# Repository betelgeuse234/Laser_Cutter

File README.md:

# Laser_Cutter
Roughly 2'x4' laser cutter with custom software and electronics hardware

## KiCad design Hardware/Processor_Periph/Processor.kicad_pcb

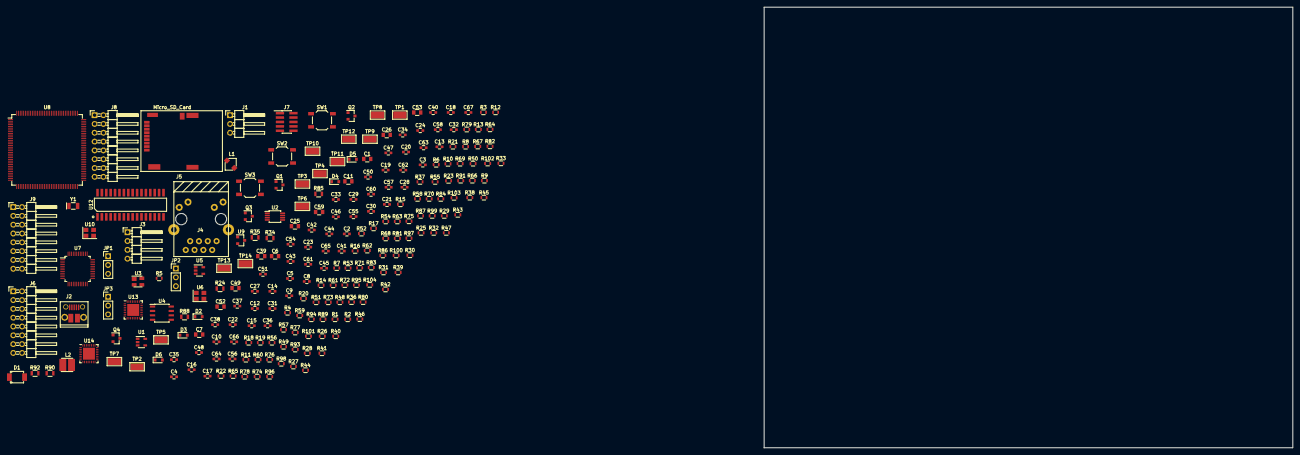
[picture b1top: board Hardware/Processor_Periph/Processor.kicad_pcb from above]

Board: 4 copper layers, 152.4 x 127.0 mm, 226 parts (0 on the bottom side), 183 nets, no tracks yet.

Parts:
C1, C25, C49, C59: 4.7uF; C_0805
C2, C4, C5, C10, C12, C14, C15, C16, C18, C19, C20, C22, C23, C24, C27, C29, C30, C31, C33, C34, C35, C37, C38, C40, C42, C43, C44, C46, C47, C48, C50, C51, C54, C55, C57, C58, C60, C61, C62, C63, C64, C65, C66, C67: 100nF; C_0603
C3: 4.5nF; C_0603
C6, C11: 1uF; C_0805
C7, C26, C39, C53: 10uF; C_0805
C8, C9: 3.9pF; C_0603
C13, C17, C21, C28, C32, C36, C41, C45, C56: 10nF; C_0603
C52: 2.2uF; C_0805
D1: PMEG6030ETP; SOD-128
D2, D3, D4, D5, D6: LED; D_0805
J1: 5V; Pin_Header_Angled_1x03_Pitch2.54mm
J2: USB_OTG; USB_Micro-B_10103594-0001LF_holes
J3: UART0; Pin_Header_Angled_1x04_Pitch2.54mm
J4: RJ-45_J0006D01BNL; J0006D01BNL
J5: Micro_SD_Card; MicroSD-Yamaichi-PJS
J6, J8, J9: CONN_SPARE; Pin_Header_Angled_2x08_Pitch2.54mm
J7: JTAGICE3-SWD; Pin_Header_Straight_2x05_Pitch1.27mm_SMD
JP1, JP2, JP3: VCC_SEL; Pin_Header_Straight_1x03_Pitch2.54mm
L1: 2.2uH; CDRH2D14
L2: 10uH; Inductor_SMD_3.0mm_x_3.0mm
Q1, Q2, Q3, Q4: BSS806NE; SOT-23
R1, R2, R3, R4, R8, R9, R10, R11, R14, R15, R16, R17, R20, R21, R22, R23, R25, R26, R27, R28, R29, R30, R31, R32, R47, R51: 2.2k; R_0603
R5: 1M; R_0603
R6, R7, R12, R13, R18, R19, R33, R44, R46, R48, R52, R54, R73, R75, R76, R77, R79, R80, R81, R82, R83, R84, R86, R87, R89, R91, R93, R94, R95, R96, R97, R98, R99, R100, R101, R102, R103, R104: 10k; R_0603
R24, R34, R35, R85, R88, R90, R92: 150R; R_0805
R36, R45, R49, R53, R56: 0R; R_0603
R37: 4.87k; R_0603
R38, R39, R41, R42: 49.9R; R_0603
R40, R43, R50, R55: 100k; R_0603
R57, R58, R59, R60, R61, R62, R63, R64, R65, R66, R67, R68, R69, R70, R71, R78: 27R; R_0603
R72: 1R; R_0603
R74: 1.5K; R_0603
SW1, SW2, SW3: PB; SW_SPST_TL3342
TP1: U0_TXD; Test_Point_Keystone_5019_Minature
TP2: U0_RXD; Test_Point_Keystone_5019_Minature
TP3: 5V; Test_Point_Keystone_5019_Minature
TP4: 3V3; Test_Point_Keystone_5019_Minature
TP5: 1V8; Test_Point_Keystone_5019_Minature
TP6: 1V2; Test_Point_Keystone_5019_Minature
TP7: XOUT_32; Test_Point_Keystone_5019_Minature
TP8: MCU_XIN; Test_Point_Keystone_5019_Minature
TP9: XIN_32; Test_Point_Keystone_5019_Minature
TP10: LED_SPEED; Test_Point_Keystone_5019_Minature
TP11: ERASE; Test_Point_Keystone_5019_Minature
TP12: PHY_XIN; Test_Point_Keystone_5019_Minature
TP13: JTAG_SEL; Test_Point_Keystone_5019_Minature
TP14: TST; Test_Point_Keystone_5019_Minature
U1: LM3671; SOT-23-5
U2: TXS0102; MSOP-8_3x3mm_Pitch0.65mm
U3: PRTR5V0U2X; SOT-143
U4: S25FL127S; SOIC-8_3.9x4.9mm_Pitch1.27mm
U5: MIC5365; SOT-23-5
U6: DSC61XX; Crystal_SMD_3225-4pin_3.2x2.5mm
U7: DP83848C; LQFP-48_7x7mm_Pitch0.5mm
U8: ATSAM4E16E; TQFP-144_20x20mm_Pitch0.5mm
U9: 3.0V; SOT-23
U10: ASE-25.000MHZ-LC-T; Crystal_SMD_3225-4pin_3.2x2.5mm
U12: CY7C1018; 32-SOJ-300mil
U13, U14: TCA6424A; QFN-32-1EP_5x5mm_Pitch0.5mm
Y1: 32.768kHz; Crystal_SMD_MicroCrystal_CC7V-T1A-2pin_3.2x1.5mm

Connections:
+1V2: C20.1, C27.1, C31.1, C35.1, C40.1, C44.1, C52.1, C55.1, L2.2, TP6.1, U8.3, U8.29, U8.33, U8.50, U8.81, U8.107, U8.123
+1V8: C11.1, C12.1, C13.1, R33.1, R36.2, TP5.1, U5.5, U6.4
+3V3: C4.1, C6.1, C7.1, C10.1, C14.1, C15.1, C16.1, C17.1, C18.1, C19.1, C21.1, C22.1, C23.1, C24.1, C25.1, C28.1, C29.1, C32.1, C33.1, C36.1, C37.1, C41.1, C42.1, C45.1, C51.1, C53.1, C54.1, C56.1, C57.1, C59.1, C62.1, C63.1, C64.1, C65.1, J4.4, J4.5, J5.4, J7.4, J9.3, J9.4, J9.13, J9.14, JP2.3, JP3.3, L1.2, R1.1, R3.1, R6.1, R8.1, R10.1, R14.1, R16.1, R18.1, R19.1, R20.1, R22.1, R24.2, R25.1, R27.1, R29.1, R31.1, R36.1, R38.1, R39.2, R40.1, R41.1, R42.2, R43.1, R44.1, R45.1, R46.1, R47.2, R48.1, R49.1, R50.1, R51.2, R52.1, R53.1, R54.1, R55.1, R56.1, R73.1, R74.1, R75.1, R76.1, R77.1, R79.1, R80.1, R81.1, R82.1, R83.1, R85.1, R86.1, R88.1, R90.1, R92.1, R93.1, R94.1, R95.1, R96.1, TP4.1, U1.4, U2.3, U2.6, U4.8, U5.1, U8.5, U8.30, U8.43, U8.72, U8.80, U8.96, U8.134, U8.143, U10.4, U12.8, U12.24, U13.31, U14.26, U14.31
+5V: C1.1, JP1.2, TP3.1, U1.1, U1.3
+5V_EXT: D1.1, JP1.1
+5V_UART: C2.1, J3.4, U2.7
+5V_USB: C5.1, J2.1, JP1.3, R7.2, U3.4
/A0: U8.111, U12.1
/A1: U8.117, U12.2
/A2: U8.120, U12.3
/A3: U8.122, U12.4
/A4: U8.124, U12.13
/A5: U8.127, U12.14
/A6: U8.130, U12.15
/A7: U8.133, U12.16
/A8: U8.13, U12.17
/A9: U8.12, U12.18
/A10: U8.76, U12.19
/A11: U8.16, U12.20
/A12: U8.15, U12.21
/A13: U8.14, U12.29
/A14: U8.24, U12.30
/A15: U8.23, U12.31
/A16: U8.22, U12.32
/AREF: C50.1, R73.2, U8.9, U9.1
/D0: U8.11, U12.6
/D1: U8.38, U12.7
/D2: U8.39, U12.10
/D3: U8.40, U12.11
/D4: U8.41, U12.22
/D5: U8.58, U12.23
/D6: U8.54, U12.26
/D7: U8.48, U12.27
/ERASE: TP11.1, U8.87
/ERX-: J4.3, J4.6, R39.1, R42.1, U7.13, U7.14
/ETX+: J4.1, R41.2, U7.17
/ETX-: J4.2, R38.2, U7.16
/GCOL: R1.2, R2.1, R68.1, U8.88
/GCOL_R: R68.2, U7.42
/GCRS: R29.2, R30.1, R69.1, U8.101
/GCRS_R: R69.2, U7.40
/GMDC: R70.1, U8.113
/GMDC_R: R70.2, U7.31
/GMDIO: R71.1, R74.2, U8.110
/GMDIO_R: R71.2, U7.30
/GPIO_01_~INT: R95.2, U8.99, U13.32
/GPIO_01_~RST: R93.2, U8.93, U13.28
/GPIO_23_~INT: R96.2, U8.73, U14.32
/GPIO_23_~RST: R94.2, U8.114, U14.28
/GRX0: R8.2, R9.1, R61.1, U8.125
/GRX0_R: R61.2, U7.43
/GRX1: R14.2, R15.1, R62.1, U8.121
/GRX1_R: R62.2, U7.44
/GRX2: R20.2, R21.1, R63.1, U8.98
/GRX2_R: R63.2, U7.45
/GRX3: R25.2, R26.1, R64.1, U8.92
/GRX3_R: R64.2, U7.46
/GRXCK: R65.1, U8.84
/GRXCK_R: R65.2, U7.38
/GRXDV: R22.2, R23.1, R67.1, U8.126
/GRXDV_R: R67.2, U7.39
/GRXER: R31.2, R32.1, R66.1, U8.119
/GRXER_R: R66.2, U7.41
/GTX0: U7.3, U8.131
/GTX1: U7.4, U8.128
/GTX2: U7.5, U8.106
/GTX3: R27.2, R28.1, U7.6, U8.78
/GTXCK: U7.1, U8.1
/GTXEN: U7.2, U8.132
/I2C_SCL: R44.2, R46.2, U8.77, U13.29, U14.29
/I2C_SDA: R52.2, R54.2, U8.91, U13.30, U14.30
/JTAG_SEL: TP13.1, U8.104
/LDO_EN: R18.2, U5.3
/LED1: Q1.1, R84.1, U8.4
/LED2: Q2.1, R87.1, U8.6
/LED3: Q3.1, R89.1, U8.7
/LED4: Q4.1, R91.1, U8.10
/LED_ACT: J4.12, R3.2, R4.1, U7.26
/LED_LN: J4.9, R10.2, R11.1, U7.28
/LED_SP: R16.2, R17.1, TP10.1, U7.27
/M0_~FLT: R99.2, U13.8
/M0_~HOM: R97.2, U13.1
/M1_~FLT: R103.2, U13.18
/M1_~HOM: R101.2, U13.11
/M2_~FLT: R100.2, U14.8
/M2_~HOM: R98.2, U14.1
/M3_~FLT: R104.2, U14.18
/M3_~HOM: R102.2, U14.11
/MCCDA: J5.3, R48.2, U8.112
/MCCDA2: J5.1, R40.2, U8.62
/MCCDA3: J5.2, R43.2, U8.70
/MCCK: J5.5, R58.2
/MCCK_R: R58.1, U8.129
/MCDA0: J5.7, R50.2, U8.116
/MCDA1: J5.8, R55.2, U8.118
/MCU_XIN: TP8.1, U8.142
/NVM_MISO: U4.2, U8.68
/NVM_MOSI: U4.5, U8.42
/NVM_SCK: R57.2, U4.6
/NVM_SCK_R: R57.1, U8.51
/NVM_~CS: R6.2, U4.1, U8.64
/NVM_~HOLD: U4.7, U8.49
/PA0: J8.7, U8.102
/PA16: J6.13, U8.45
/PA17: J6.8, U8.25
/PA21: J6.11, U8.32
/PA22: J6.12, U8.37
/PA23: J6.14, U8.46
/PA24: J8.3, U8.56
/PA25: J8.4, U8.59
/PB0: J6.7, U8.21
/PB2: J6.9, U8.26
/PB3: J6.10, U8.31
/PB4: J8.8, U8.105
/PB13: J6.6, J8.10, U8.144
/PB14: J8.9, U8.140
/PC12: J6.3, U8.17
/PC13: J6.5, U8.19
/PC15: J6.4, U8.18
/PC16: J8.6, U8.100
/PC17: J8.5, U8.103
/PFBIN1: C34.1, U7.18
/PFBIN2: C38.1, U7.37
/PFBOUT: C26.1, C30.1, U7.23
/PHY_XIN: TP12.1, U7.34, U10.3
/PHY_~INT: R75.2, U7.7, U8.67
/PHY_~RST: R77.2, U7.29, U8.69
/RAM_~CS: R83.2, U8.97, U12.5
/RAM_~RD: R81.2, U8.94, U12.28
/RAM_~WE: R82.2, U8.82, U12.12
/RBIAS: R37.1, U7.24
/SPARE0: J9.5, U13.21
/SPARE1: J9.7, U13.22
/SPARE2: J9.9, U13.23
/SPARE3: J9.11, U13.24
/SPARE4: J9.6, U14.21
/SPARE5: J9.8, U14.22
/SPARE6: J9.10, U14.23
/SPARE7: J9.12, U14.24
/SW1: C61.1, R80.2, SW3.1, U8.27
/SW2: C60.1, R79.2, SW2.1, U8.28
/SWDCLK: J7.1, R86.2, U8.89
/SWDIO: J7.5, U8.79
/SWO: J7.3, U8.109
/TST: TP14.1, U8.85
/U0_RXD: TP2.1, U2.5, U8.75
/U0_TXD: R19.2, TP1.1, U2.4, U8.66
/UART_RXD: J3.2, U2.1
/UART_TXD: J3.3, U2.8
/USBD+: J2.3, R60.2, U3.3
/USBD-: J2.2, R59.2, U3.2
/USBD_R+: R60.1, U8.137
/USBD_R-: R59.1, U8.136
/VBUS_DET: R7.1, R12.1, U8.2
/VDDPLL: C48.1, L2.1, R72.1, U8.139
/XIN32: C8.1, TP9.1, U8.35, Y1.1
/XOUT32: C9.1, TP7.1, U8.36, Y1.2
/~RST: C58.1, J7.6, R78.1, SW1.1
/~RST_R: R78.2, U8.83
GND: C1.2, C2.2, C3.1, C4.2, C5.2, C6.2, C7.2, C8.2, C9.2, C10.2, C11.2, C12.2, C13.2, C14.2, C15.2, C16.2, C17.2, C18.2, C19.2, C20.2, C21.2, C22.2, C23.2, C24.2, C25.2, C26.2, C27.2, C28.2, C29.2, C30.2, C31.2, C32.2, C33.2, C34.2, C35.2, C36.2, C37.2, C38.2, C39.2, C40.2, C41.2, C42.2, C43.2, C44.2, C45.2, C46.2, C47.2, C48.2, C49.2, C50.2, C51.2, C52.2, C53.2, C54.2, C55.2, C56.2, C57.2, C58.2, C59.2, C60.2, C61.2, C62.2, C63.2, C64.2, C65.2, C66.2, C67.2, D2.1, J1.2, J1.3, J2.5, J3.1, J4.8, J4.13, J5.6, J6.1, J6.2, J6.15, J6.16, J7.2, J8.1, J8.2, J8.15, J8.16, J9.1, J9.2, J9.15, J9.16, Q1.2, Q2.2, Q3.2, Q4.2, R2.2, R4.2, R5.1, R9.2, R11.2, R13.2, R15.2, R17.2, R21.2, R23.2, R26.2, R28.2, R30.2, R32.2, R34.1, R35.1, R37.2, R84.2, R87.2, R89.2, R91.2, SW1.2, SW2.2, SW3.2, U1.2, U2.2, U4.4, U5.2, U6.2, U7.15, U7.19, U7.35, U7.36, U7.47, U8.8, U8.44, U8.61, U8.95, U8.115, U8.135, U8.138, U9.2, U10.2, U12.9, U12.25, U13.25, U13.26, U14.25
unnamed: C3.2, J2.6, R5.2, U3.1
unnamed: C39.1, C43.1, C46.1, C47.1, R45.2, R49.2, R53.2, R56.2, U7.22, U7.32, U7.48
unnamed: C49.1, R72.2
unnamed: C66.1, JP2.2, R97.1, R99.1, R101.1, R103.1, U13.27
unnamed: C67.1, JP3.2, R98.1, R100.1, R102.1, R104.1, U14.27
unnamed: D1.2, J1.1
unnamed: D2.2, R24.1
unnamed: D3.1, Q1.3
unnamed: D3.2, R85.2
unnamed: D4.1, Q2.3
unnamed: D4.2, R88.2
unnamed: D5.1, Q3.3
unnamed: D5.2, R90.2
unnamed: D6.1, Q4.3
unnamed: D6.2, R92.2
unnamed: J4.10, R34.2
unnamed: J4.11, R35.2
unnamed: L1.1, U1.5
unnamed: R12.2, R13.1
unnamed: R33.2, U6.1
unnamed: R47.1, U7.21
unnamed: R51.1, U7.20
unnamed: R76.2, U10.1

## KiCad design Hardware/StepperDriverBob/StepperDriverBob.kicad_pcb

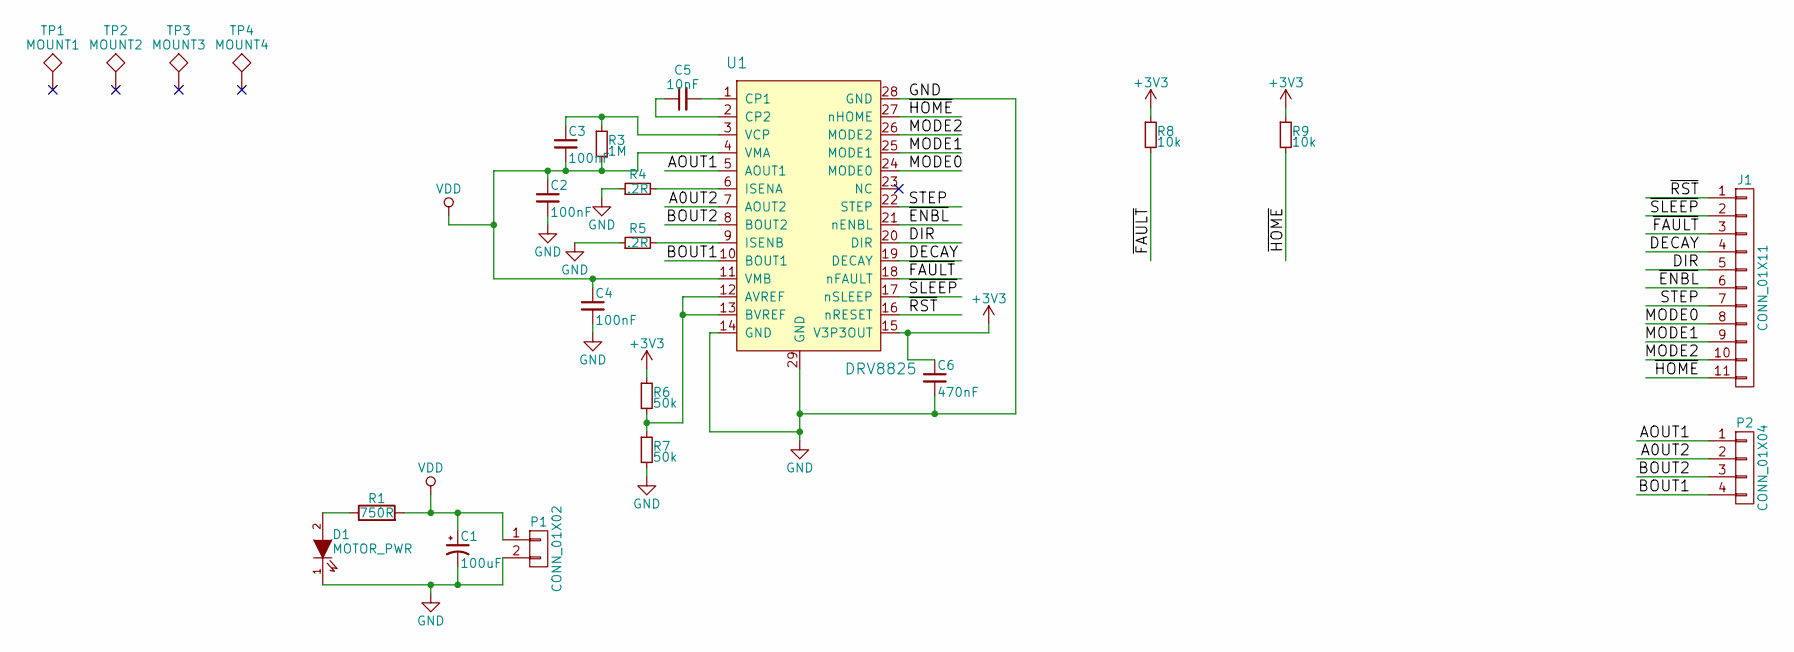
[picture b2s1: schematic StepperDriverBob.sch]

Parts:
C1: 100uF; CP_Elec_10x10
C2, C3, C4: 100nF; C_0603
C5: 10nF; C_0603
C6: 470nF; C_0603
D1: MOTOR_PWR; LED_0603
J1: CONN_01X11; Pin_Header_Straight_1x11_Pitch2.54mm
P1: CONN_01X02; Pin_Header_Straight_1x02_Pitch2.54mm
P2: CONN_01X04; Pin_Header_Straight_1x04_Pitch2.54mm
R1: 750R; R_0603
R3: 1M; R_0603
R4, R5: .2R; R_2010
R6, R7: 50k; Pin_Header_Straight_1x02_Pitch2.54mm
R8, R9: 10k; R_0603
TP1: MOUNT1; MountingHole_3.2mm_M3_Pad
TP2: MOUNT2; MountingHole_3.2mm_M3_Pad
TP3: MOUNT3; MountingHole_3.2mm_M3_Pad
TP4: MOUNT4; MountingHole_3.2mm_M3_Pad
U1: DRV8825; HTSSOP-28_4.4x9.7mm_Pitch0.65mm_ThermalPad

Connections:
+3V3: C6.1, R6.1, R8.1, R9.1, U1.15 (V3P3OUT)
/A0UT2: P2.2, U1.7 (AOUT2)
/AOUT1: P2.1, U1.5 (AOUT1)
/BOUT1: P2.4, U1.10 (BOUT1)
/BOUT2: P2.3, U1.8 (BOUT2)
/DECAY: J1.4, U1.19 (DECAY)
/DIR: J1.5, U1.20 (DIR)
/MODE0: J1.8, U1.24 (MODE0)
/MODE1: J1.9, U1.25 (MODE1)
/MODE2: J1.10, U1.26 (MODE2)
/STEP: J1.7, U1.22 (STEP)
/~ENBL~: J1.6, U1.21 (nENBL)
/~FAULT~: J1.3, R8.2, U1.18 (nFAULT)
/~HOME~: J1.11, R9.2, U1.27 (nHOME)
/~RST~: J1.1, U1.16 (nRESET)
/~SLEEP~: J1.2, U1.17 (nSLEEP)
GND: C1.2, C2.2, C4.2, C6.2, D1.1 (K), P1.2, R4.1, R5.1, R7.2, U1.14 (GND), U1.28 (GND), U1.29 (GND)
unnamed: C3.1, R3.1, U1.3 (VCP)
unnamed: C5.1, U1.2 (CP2)
unnamed: C5.2, U1.1 (CP1)
unnamed: D1.2 (A), R1.1
unnamed: R4.2, U1.6 (ISENA)
unnamed: R5.2, U1.9 (ISENB)
unnamed: R6.2, R7.1, U1.12 (AVREF), U1.13 (BVREF)
VDD: C1.1, C2.1, C3.2, C4.1, P1.1, R1.2, R3.2, U1.4 (VMA), U1.11 (VMB)

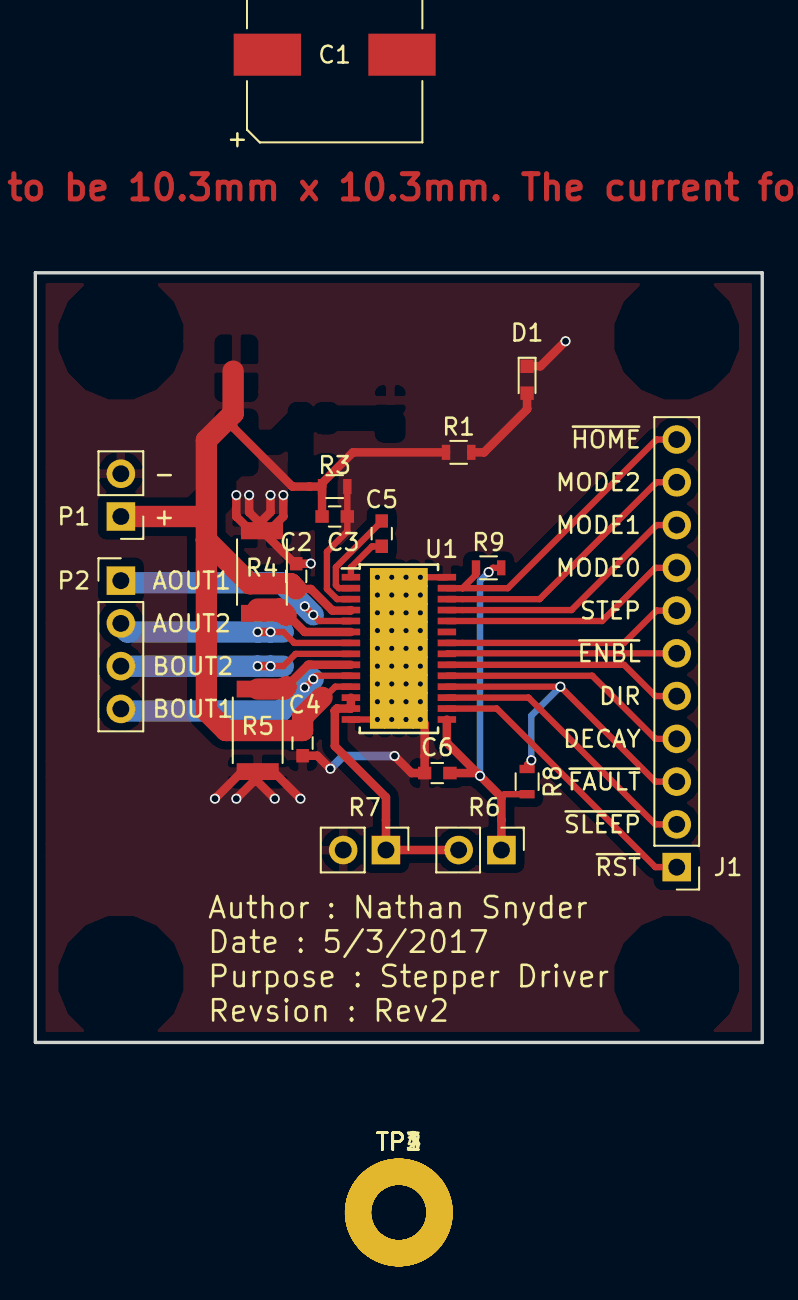
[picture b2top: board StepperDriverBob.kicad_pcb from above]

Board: 2 copper layers, 43.2 x 45.7 mm, 23 parts (0 on the bottom side), 25 nets.

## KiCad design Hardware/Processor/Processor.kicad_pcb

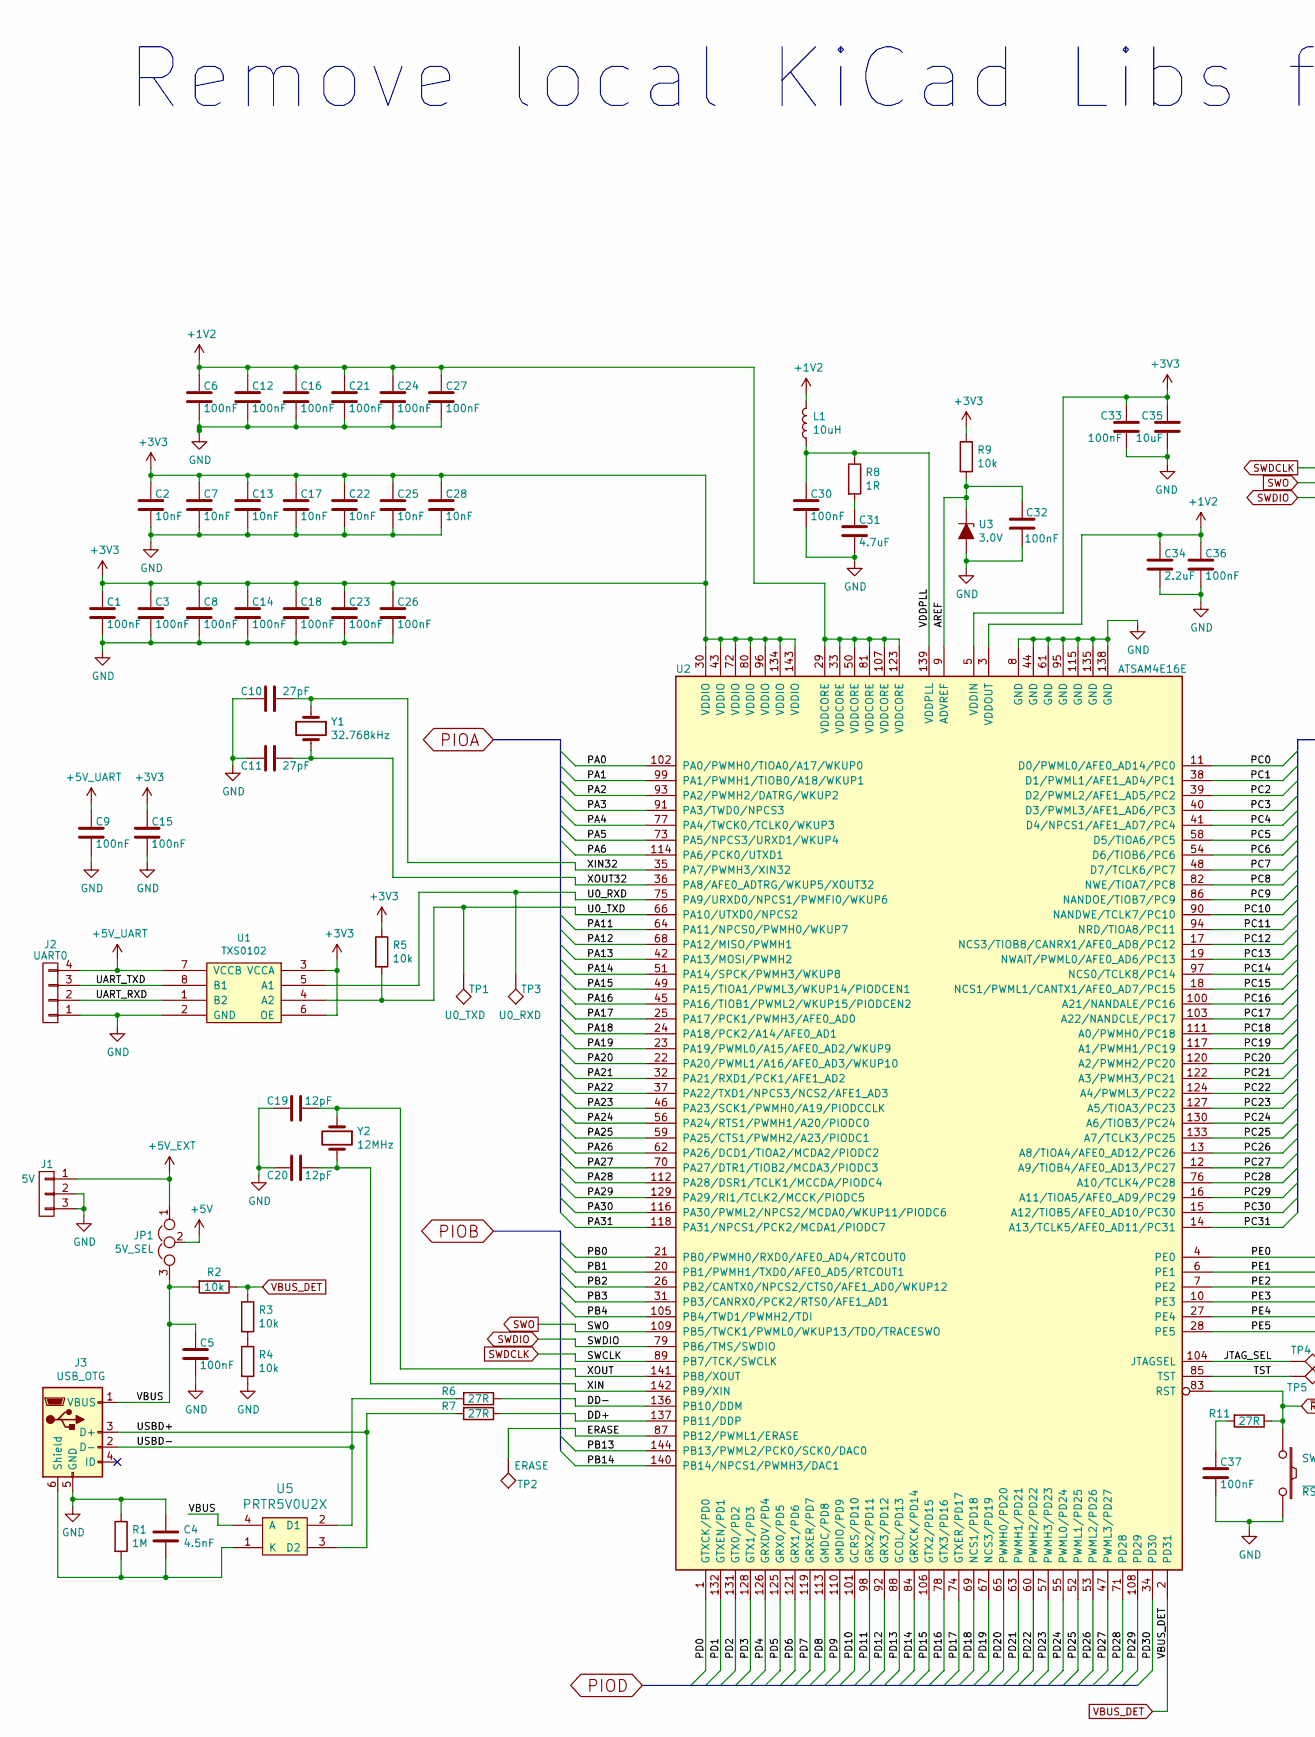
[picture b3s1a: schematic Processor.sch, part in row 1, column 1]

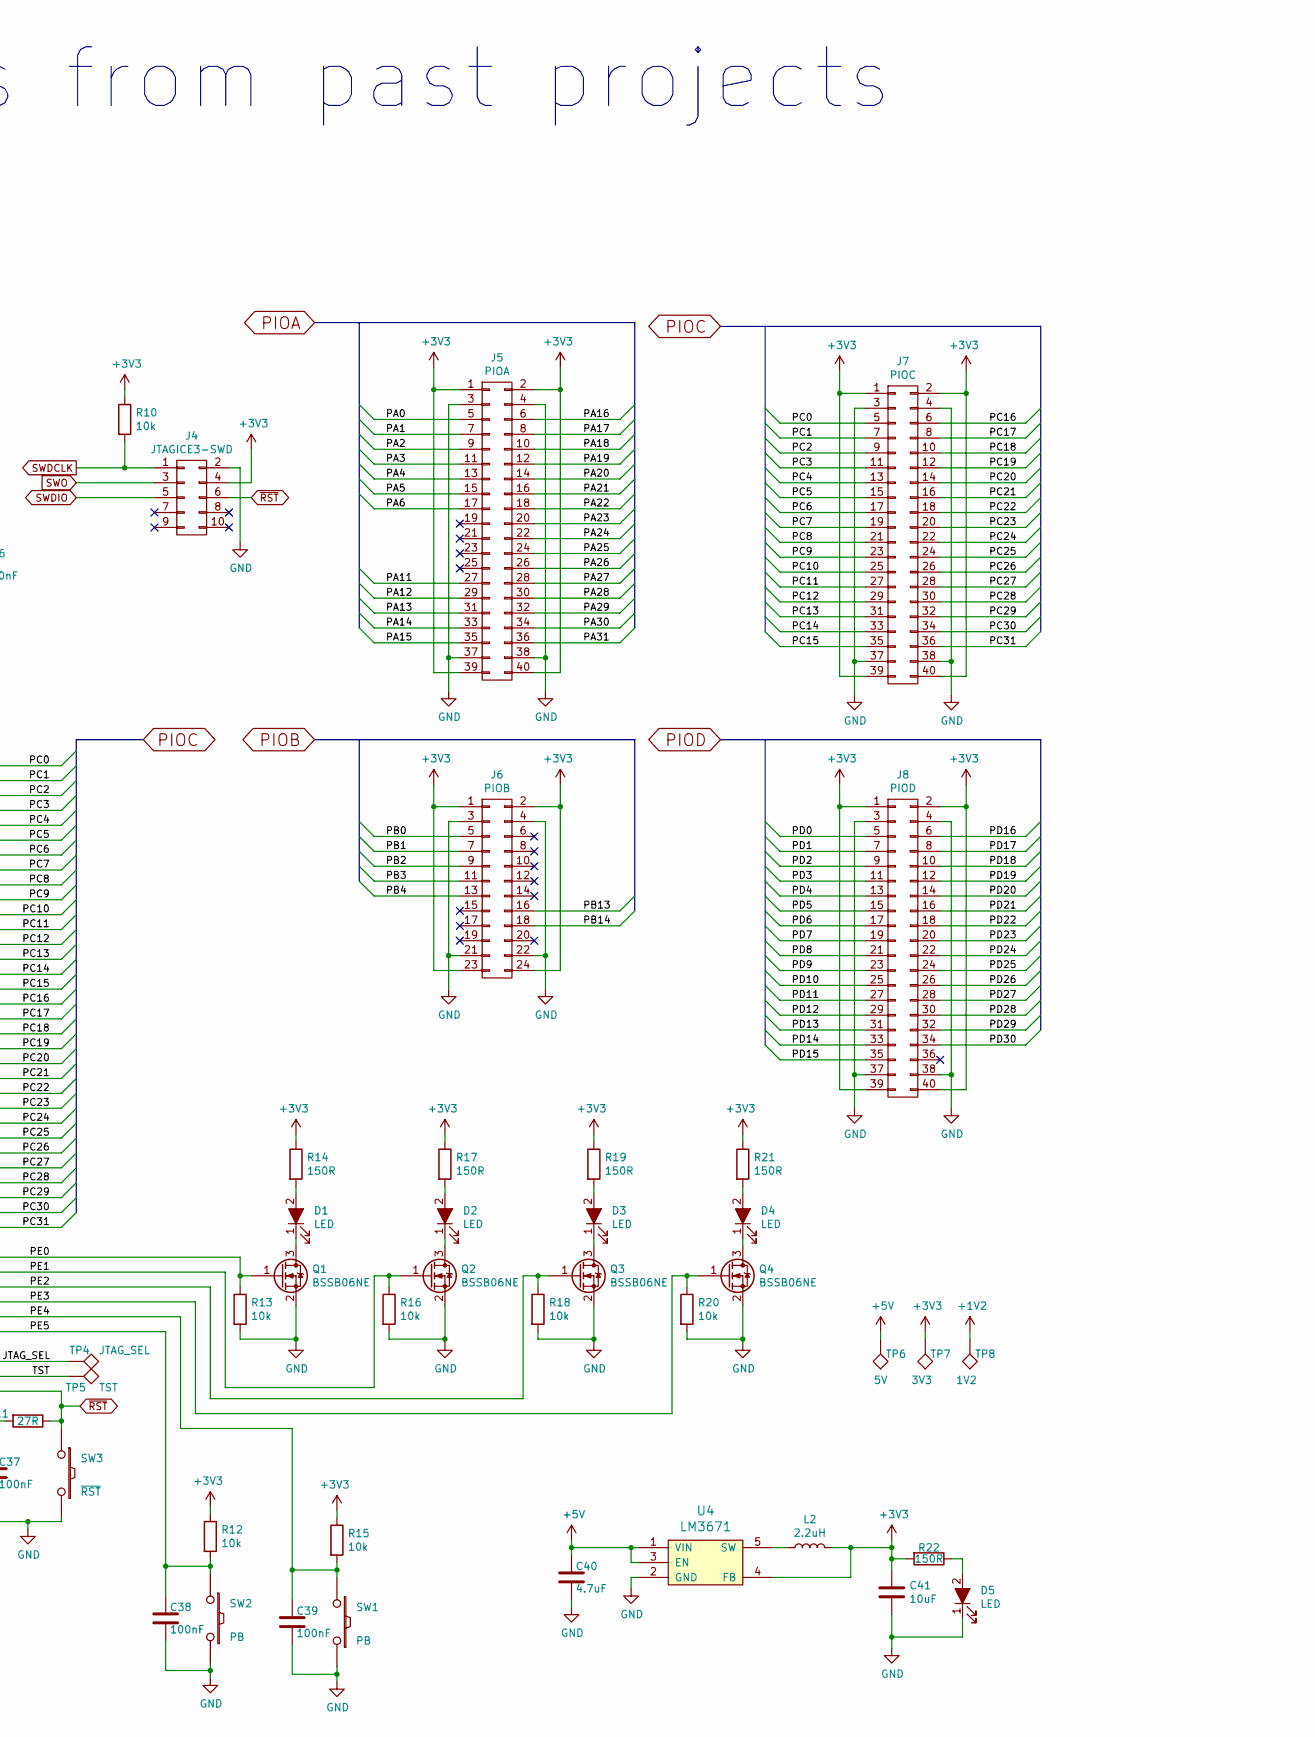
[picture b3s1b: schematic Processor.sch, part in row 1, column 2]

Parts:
C1, C3, C5, C6, C8, C9, C12, C14, C15, C16, C18, C21, C23, C24, C26, C27, C30, C32, C33, C36, C37, C38, C39: 100nF; C_0603
C2, C7, C13, C17, C22, C25, C28: 10nF; C_0603
C4: 4.5nF; C_0603
C10, C11: 27pF; C_0603
C19, C20: 12pF; C_0603
C31, C40: 4.7uF; C_0805
C34: 2.2uF; C_0805
C35, C41: 10uF; C_0805
D1, D2, D3, D4, D5: LED; LED_0805
J1: 5V; ConnectorSMD-1x3
J2: UART0; ConnectorSMD-1x4
J3: USB_OTG; conn_usb_B_micro_smd
J4: JTAGICE3-SWD; ConnectorMicromatch-10
J5: PIOA; ConnectorSMD-40
J6: PIOB; ConnectorSMD-24
J7: PIOC; ConnectorSMD-40
J8: PIOD; ConnectorSMD-40
JP1: 5V_SEL; ConnectorSMD-1x3
L1: 10uH; Inductor_3mmx3mm
L2: 2.2uH; Inductor_1212
Q1, Q2, Q3, Q4: BSSB06NE; SOT-23
R1: 1M; C_0603
R2, R3, R4, R5, R9, R10, R12, R13, R15, R16, R18, R20: 10k; C_0603
R6, R7, R11: 27R; C_0603
R8: 1R; C_0603
R14, R17, R19, R21, R22: 150R; C_0805
SW1, SW2: PB; SW_SPST_TL3342
SW3: ~RST; SW_SPST_TL3342
TP1: U0_TXD; Measurement_Point_Round-SMD-Pad_Small
TP2: ERASE; Measurement_Point_Round-SMD-Pad_Small
TP3: U0_RXD; Measurement_Point_Round-SMD-Pad_Small
TP4: JTAG_SEL; Measurement_Point_Round-SMD-Pad_Small
TP5: TST; Measurement_Point_Round-SMD-Pad_Small
TP6: 5V; Measurement_Point_Round-SMD-Pad_Small
TP7: 3V3; Measurement_Point_Round-SMD-Pad_Small
TP8: 1V2; Measurement_Point_Round-SMD-Pad_Small
U1: TXS0102; MSOP-8_3x3mm_Pitch0.65mm
U2: ATSAM4E16E; TQFP-144_20x20mm_Pitch0.5mm
U3: 3.0V; SOT-23; MFG# LM4040C30
U4: LM3671; SOT-23-5
U5: PRTR5V0U2X; SOT143B
Y1: 32.768kHz; FC-135R
Y2: 12MHz; Crystal_HC49-SD_SMD

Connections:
+1V2: C6.1, C12.1, C16.1, C21.1, C24.1, C27.1, C34.1, C36.1, L1.2, TP8.1, U2.3 (VDDOUT), U2.29 (VDDCORE), U2.33 (VDDCORE), U2.50 (VDDCORE), U2.81 (VDDCORE), U2.107 (VDDCORE), U2.123 (VDDCORE)
+3V3: C1.1, C2.1, C3.1, C7.1, C8.1, C13.1, C14.1, C15.1, C17.1, C18.1, C22.1, C23.1, C25.1, C26.1, C28.1, C33.1, C35.1, C41.1, J4.4, J5.1, J5.2, J5.39, J5.40, J6.1, J6.2, J6.23, J6.24, J7.1, J7.2, J7.39, J7.40, J8.1, J8.2, J8.39, J8.40, L2.2, R5.1, R9.1, R10.1, R12.1, R14.1, R15.1, R17.1, R19.1, R21.1, R22.2, TP7.1, U1.3 (VCCA), U1.6 (OE), U2.5 (VDDIN), U2.30 (VDDIO), U2.43 (VDDIO), U2.72 (VDDIO), U2.80 (VDDIO), U2.96 (VDDIO), U2.134 (VDDIO), U2.143 (VDDIO), U4.4 (FB)
+5V: C40.1, JP1.2, TP6.1, U4.1 (VIN), U4.3 (EN)
+5V_EXT: J1.1, JP1.1
+5V_UART: C9.1, J2.4, U1.7 (VCCB)
/AREF: C32.1, R9.2, U2.9 (ADVREF), U3.1 (K)
/DD+: R7.1, U2.137 (PB11/DDP)
/DD-: R6.1, U2.136 (PB10/DDM)
/ERASE: TP2.1, U2.87 (PB12/PWML1/ERASE)
/JTAG_SEL: TP4.1, U2.104 (JTAGSEL)
/PA0: J5.5, U2.102 (PA0/PWMH0/TIOA0/A17/WKUP0)
/PA1: J5.7, U2.99 (PA1/PWMH1/TIOB0/A18/WKUP1)
/PA2: J5.9, U2.93 (PA2/PWMH2/DATRG/WKUP2)
/PA3: J5.11, U2.91 (PA3/TWD0/NPCS3)
/PA4: J5.13, U2.77 (PA4/TWCK0/TCLK0/WKUP3)
/PA5: J5.15, U2.73 (PA5/NPCS3/URXD1/WKUP4)
/PA6: J5.17, U2.114 (PA6/PCK0/UTXD1)
/PA11: J5.27, U2.64 (PA11/NPCS0/PWMH0/WKUP7)
/PA12: J5.29, U2.68 (PA12/MISO/PWMH1)
/PA13: J5.31, U2.42 (PA13/MOSI/PWMH2)
/PA14: J5.33, U2.51 (PA14/SPCK/PWMH3/WKUP8)
/PA15: J5.35, U2.49 (PA15/TIOA1/PWML3/WKUP14/PIODCEN1)
/PA16: J5.6, U2.45 (PA16/TIOB1/PWML2/WKUP15/PIODCEN2)
/PA17: J5.8, U2.25 (PA17/PCK1/PWMH3/AFE0_AD0)
/PA18: J5.10, U2.24 (PA18/PCK2/A14/AFE0_AD1)
/PA19: J5.12, U2.23 (PA19/PWML0/A15/AFE0_AD2/WKUP9)
/PA20: J5.14, U2.22 (PA20/PWML1/A16/AFE0_AD3/WKUP10)
/PA21: J5.16, U2.32 (PA21/RXD1/PCK1/AFE1_AD2)
/PA22: J5.18, U2.37 (PA22/TXD1/NPCS3/NCS2/AFE1_AD3)
/PA23: J5.20, U2.46 (PA23/SCK1/PWMH0/A19/PIODCCLK)
/PA24: J5.22, U2.56 (PA24/RTS1/PWMH1/A20/PIODC0)
/PA25: J5.24, U2.59 (PA25/CTS1/PWMH2/A23/PIODC1)
/PA26: J5.26, U2.62 (PA26/DCD1/TIOA2/MCDA2/PIODC2)
/PA27: J5.28, U2.70 (PA27/DTR1/TIOB2/MCDA3/PIODC3)
/PA28: J5.30, U2.112 (PA28/DSR1/TCLK1/MCCDA/PIODC4)
/PA29: J5.32, U2.129 (PA29/RI1/TCLK2/MCCK/PIODC5)
/PA30: J5.34, U2.116 (PA30/PWML2/NPCS2/MCDA0/WKUP11/PIODC6)
/PA31: J5.36, U2.118 (PA31/NPCS1/PCK2/MCDA1/PIODC7)
/PB0: J6.5, U2.21 (PB0/PWMH0/RXD0/AFE0_AD4/RTCOUT0)
/PB1: J6.7, U2.20 (PB1/PWMH1/TXD0/AFE0_AD5/RTCOUT1)
/PB2: J6.9, U2.26 (PB2/CANTX0/NPCS2/CTS0/AFE1_AD0/WKUP12)
/PB3: J6.11, U2.31 (PB3/CANRX0/PCK2/RTS0/AFE1_AD1)
/PB4: J6.13, U2.105 (PB4/TWD1/PWMH2/TDI)
/PB13: J6.16, U2.144 (PB13/PWML2/PCK0/SCK0/DAC0)
/PB14: J6.18, U2.140 (PB14/NPCS1/PWMH3/DAC1)
/PC0: J7.5, U2.11 (D0/PWML0/AFE0_AD14/PC0)
/PC1: J7.7, U2.38 (D1/PWML1/AFE1_AD4/PC1)
/PC2: J7.9, U2.39 (D2/PWML2/AFE1_AD5/PC2)
/PC3: J7.11, U2.40 (D3/PWML3/AFE1_AD6/PC3)
/PC4: J7.13, U2.41 (D4/NPCS1/AFE1_AD7/PC4)
/PC5: J7.15, U2.58 (D5/TIOA6/PC5)
/PC6: J7.17, U2.54 (D6/TIOB6/PC6)
/PC7: J7.19, U2.48 (D7/TCLK6/PC7)
/PC8: J7.21, U2.82 (NWE/TIOA7/PC8)
/PC9: J7.23, U2.86 (NANDOE/TIOB7/PC9)
/PC10: J7.25, U2.90 (NANDWE/TCLK7/PC10)
/PC11: J7.27, U2.94 (NRD/TIOA8/PC11)
/PC12: J7.29, U2.17 (NCS3/TIOB8/CANRX1/AFE0_AD8/PC12)
/PC13: J7.31, U2.19 (NWAIT/PWML0/AFE0_AD6/PC13)
/PC14: J7.33, U2.97 (NCS0/TCLK8/PC14)
/PC15: J7.35, U2.18 (NCS1/PWML1/CANTX1/AFE0_AD7/PC15)
/PC16: J7.6, U2.100 (A21/NANDALE/PC16)
/PC17: J7.8, U2.103 (A22/NANDCLE/PC17)
/PC18: J7.10, U2.111 (A0/PWMH0/PC18)
/PC19: J7.12, U2.117 (A1/PWMH1/PC19)
/PC20: J7.14, U2.120 (A2/PWMH2/PC20)
/PC21: J7.16, U2.122 (A3/PWMH3/PC21)
/PC22: J7.18, U2.124 (A4/PWML3/PC22)
/PC23: J7.20, U2.127 (A5/TIOA3/PC23)
/PC24: J7.22, U2.130 (A6/TIOB3/PC24)
/PC25: J7.24, U2.133 (A7/TCLK3/PC25)
/PC26: J7.26, U2.13 (A8/TIOA4/AFE0_AD12/PC26)
/PC27: J7.28, U2.12 (A9/TIOB4/AFE0_AD13/PC27)
/PC28: J7.30, U2.76 (A10/TCLK4/PC28)
/PC29: J7.32, U2.16 (A11/TIOA5/AFE0_AD9/PC29)
/PC30: J7.34, U2.15 (A12/TIOB5/AFE0_AD10/PC30)
/PC31: J7.36, U2.14 (A13/TCLK5/AFE0_AD11/PC31)
/PD0: J8.5, U2.1 (GTXCK/PD0)
/PD1: J8.7, U2.132 (GTXEN/PD1)
/PD2: J8.9, U2.131 (GTX0/PD2)
/PD3: J8.11, U2.128 (GTX1/PD3)
/PD4: J8.13, U2.126 (GRXDV/PD4)
/PD5: J8.15, U2.125 (GRX0/PD5)
/PD6: J8.17, U2.121 (GRX1/PD6)
/PD7: J8.19, U2.119 (GRXER/PD7)
/PD8: J8.21, U2.113 (GMDC/PD8)
/PD9: J8.23, U2.110 (GMDIO/PD9)
/PD10: J8.25, U2.101 (GCRS/PD10)
/PD11: J8.27, U2.98 (GRX2/PD11)
/PD12: J8.29, U2.92 (GRX3/PD12)
/PD13: J8.31, U2.88 (GCOL/PD13)
/PD14: J8.33, U2.84 (GRXCK/PD14)
/PD15: J8.35, U2.106 (GTX2/PD15)
/PD16: J8.6, U2.78 (GTX3/PD16)
/PD17: J8.8, U2.74 (GTXER/PD17)
/PD18: J8.10, U2.69 (NCS1/PD18)
/PD19: J8.12, U2.67 (NCS3/PD19)
/PD20: J8.14, U2.65 (PWMH0/PD20)
/PD21: J8.16, U2.63 (PWMH1/PD21)
/PD22: J8.18, U2.60 (PWMH2/PD22)
/PD23: J8.20, U2.57 (PWMH3/PD23)
/PD24: J8.22, U2.55 (PWML0/PD24)
/PD25: J8.24, U2.52 (PWML1/PD25)
/PD26: J8.26, U2.53 (PWML2/PD26)
/PD27: J8.28, U2.47 (PWML3/PD27)
/PD28: J8.30, U2.71 (PD28)
/PD29: J8.32, U2.108 (PD29)
/PD30: J8.34, U2.34 (PD30)
/PE0: Q1.1 (G), R13.1, U2.4 (PE0)
/PE1: Q2.1 (G), R16.1, U2.6 (PE1)
/PE2: Q3.1 (G), R18.1, U2.7 (PE2)
/PE3: Q4.1 (G), R20.1, U2.10 (PE3)
/PE4: C39.1, R15.2, SW1.1, U2.27 (PE4)
/PE5: C38.1, R12.2, SW2.1, U2.28 (PE5)
/TST: TP5.1, U2.85 (TST)
/U0_RXD: TP3.1, U1.5 (A1), U2.75 (PA9/URXD0/NPCS1/PWMFI0/WKUP6)
/U0_TXD: R5.2, TP1.1, U1.4 (A2), U2.66 (PA10/UTXD0/NPCS2)
/UART_RXD: J2.2, U1.1 (B2)
/UART_TXD: J2.3, U1.8 (B1)
/USBD+: J3.3 (D+), R7.2, U5.3 (D2)
/USBD-: J3.2 (D-), R6.2, U5.2 (D1)
/VBUS: C5.1, J3.1 (VBUS), JP1.3, R2.2, U5.4 (A)
/VDDPLL: C30.1, L1.1, R8.1, U2.139 (VDDPLL)
/XIN: C20.1, U2.142 (PB9/XIN), Y2.2
/XIN32: C10.1, U2.35 (PA7/PWMH3/XIN32), Y1.1
/XOUT: C19.1, U2.141 (PB8/XOUT), Y2.1
/XOUT32: C11.1, U2.36 (PA8/AFE0_ADTRG/WKUP5/XOUT32), Y1.2
GND: C1.2, C2.2, C3.2, C4.1, C5.2, C6.2, C7.2, C8.2, C9.2, C10.2, C11.2, C12.2, C13.2, C14.2, C15.2, C16.2, C17.2, C18.2, C19.2, C20.2, C21.2, C22.2, C23.2, C24.2, C25.2, C26.2, C27.2, C28.2, C30.2, C31.2, C32.2, C33.2, C34.2, C35.2, C36.2, C37.2, C38.2, C39.2, C40.2, C41.2, D5.1 (K), J1.2, J1.3, J2.1, J3.5 (GND), J4.2, J5.3, J5.4, J5.37, J5.38, J6.3, J6.4, J6.21, J6.22, J7.3, J7.4, J7.37, J7.38, J8.3, J8.4, J8.37, J8.38, Q1.2 (S), Q2.2 (S), Q3.2 (S), Q4.2 (S), R1.1, R4.2, R13.2, R16.2, R18.2, R20.2, SW1.2, SW2.2, SW3.2, U1.2 (GND), U2.8 (GND), U2.44 (GND), U2.61 (GND), U2.95 (GND), U2.115 (GND), U2.135 (GND), U2.138 (GND), U3.2 (A), U4.2 (GND)
unnamed: C4.2, J3.6 (Shield), R1.2, U5.1 (K)
unnamed: C31.1, R8.2
unnamed: C37.1, R11.2
unnamed: D1.1 (K), Q1.3 (D)
unnamed: D1.2 (A), R14.2
unnamed: D2.1 (K), Q2.3 (D)
unnamed: D2.2 (A), R17.2
unnamed: D3.1 (K), Q3.3 (D)
unnamed: D3.2 (A), R19.2
unnamed: D4.1 (K), Q4.3 (D)
unnamed: D4.2 (A), R21.2
unnamed: D5.2 (A), R22.1
unnamed: L2.1, U4.5 (SW)
unnamed: R3.2, R4.1
SWDCLK: J4.1, R10.2, U2.89 (PB7/TCK/SWCLK)
SWDIO: J4.5, U2.79 (PB6/TMS/SWDIO)
SWO: J4.3, U2.109 (PB5/TWCK1/PWML0/WKUP13/TDO/TRACESWO)
VBUS_DET: R2.1, R3.1, U2.2 (PD31)
~RST: J4.6, R11.1, SW3.1, U2.83 (RST)

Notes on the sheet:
Remove local KiCad Libs from past projects

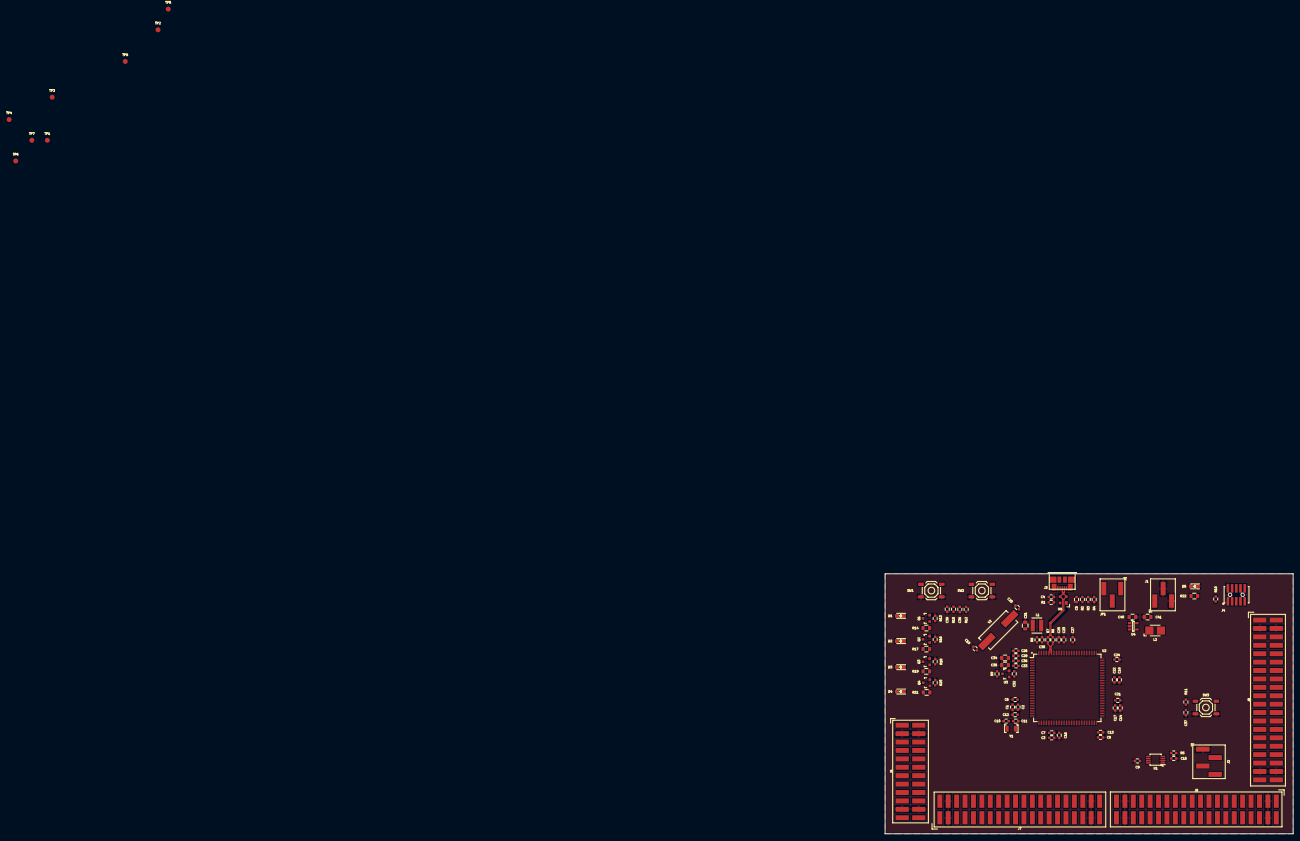
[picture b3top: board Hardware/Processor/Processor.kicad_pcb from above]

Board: 4 copper layers, 123.2 x 78.5 mm, 100 parts (0 on the bottom side), 147 nets.

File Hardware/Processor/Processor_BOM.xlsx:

| Reference | Quantity | 3x Quantity | Value | Footprint | MFG# | DigiKey# | Comments
 | C10 C11 | 2 | 6 | 27 pF | 0603 | C0603C270F5GACTU | 399-7888-1-ND
 | C19 C20 | 2 | 6 | 12pF | 0603 | CL10C120FB8NNNC | 1276-2175-1-ND
 | C1 C12 C14 C15 C16 C18 C21 C23 C24 C26 C27 C3 C30 C32 C33 C36 C37 C38 C39 C5 C6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 | 23 | 69 | 100nF | 0603 | C0603C104M5RACTU | 399-7845-1-ND | C29 no longer exists
 | C34 | 1 | 3 | 2.2uF | 0805 | GRM21BR60J225KA01L | 490-1712-1-ND
 | C4 | 1 | 3 | 4.5nF | 0603 | CL10B472KB8NNNC | 1276-1098-1-ND
 | C31 C40 | 2 | 6 | 4.7uF | 0805 | GRM21BR60J475KA11L | 490-9749-1-ND
 | C35 C41 | 2 | 6 | 10uF | 0805 | GRM21BR60J106KE19L | 490-1717-1-ND
 | C13 C17 C2 C22 C25 C28 C7 | 7 | 21 | 10nF | 0603 | CC0603KRX7R9BB103 | 311-1085-1-ND
 | D1 D2 D3 D4 D5 | 5 | 15 | LED | 0805 | LTST-C170KSKT | 160-1416-1-ND | Yellow
 | J1 TP6 | 2 | 6 | 5V | 1x3 Male Header | 961120-6300-AR-PR | 3M9492CT-ND | Surface Mount
 | J2 | 1 | 3 | UART0 | 1x4 Male Header | - | - | Uses leftover pins of J1
 | J3 | 1 | 3 | USB_OTG | USB Micro SMT | 10118192-0001LF | 609-4613-1-ND
 | J4 | 1 | 3 | JTAGICE3-SWD | 2x10 Male Header | 20021121-00010T4LF | 609-3729-ND | Surface Mount, 0.05" pitch
 | J5 | 1 | 3 | PIOA | 2x20 Male Header | 961240-6300-AR-PR | 3M9499CT-ND | Surface Mount
 | J6 | 1 | 3 | PIOB | 2x12 Male Header | 961224-6300-AR-PR | 3M9497CT-ND | Surface Mount
 | J7 | 1 | 3 | PIOC | 2x20 Male Header |  | 3M9499CT-ND | Surface Mount
 | J8 | 1 | 3 | PIOD | 2x20 Male Header | 961240-6300-AR-PR | 3M9499CT-ND | Surface Mount
 | JP1 | 1 | 3 | 5V_SEL | 1x3 Male Header | - | - | Uses leftover pins of J1
 | L1 | 1 | 3 | 10uH | Custom | LQH3NPN100MJ0L | 490-11681-1-ND
 | L2 | 1 | 3 | 2.2uH | Custom | CDRH2D14NP-2R2NC | 308-2294-1-ND
 | Q1 Q2 Q3 Q4 | 4 | 12 | BSSB06NE | SOT-23 | BSS806NEH6327XTSA1 | BSS806NEH6327XTSA1CT-ND | Check pinout at footprint assignment
 | R1 | 1 | 3 | 1M | 0603 | RC0603JR-071ML | 311-1.0MGRCT-ND
 | R14 R17 R19 R21 R22 | 5 | 15 | 150R | 0805 | 311-150ARCT-ND | 311-150ARCT-ND | 1/8 Watt
 | R11 R6 R7 | 3 | 9 | 27R | 0603 | RC0603FR-0727RL | 311-27.0HRCT-ND
 | R8 | 1 | 3 | 1R | 0603 | RC0603JR-071RL | 311-1.0GRCT-ND
 | R10 R12 R13 R15 R16 R18 R2 R20 R3 R4 R5 R9 | 12 | 36 | 10k | 0603 | RC0603JR-0710KL | 311-10KGRCT-ND
 | SW1 SW2 | 2 | 6 | PB | 3342 | TL3342F160QG/TR | EG2531CT-ND
 | SW3 | 1 | 3 | ~RST | 3342 | TL3342F160QG/TR | EG2531CT-ND
 | U1 | 1 | 3 | TXS0102 | MSOP-8 | TXS0102DCTT | 296-32603-1-ND
 | U2 | 1 | 3 | ATSAM4E16E | TQFP-144 (20x20) | ATSAM4E16EA-AUR | ATSAM4E16EA-AURCT-ND
 | U3 | 1 | 3 | 3.0V | SOT-23 | LM4040C30IDBZR | 296-20887-1-ND | Check pinout at footprint assignment
 | U4 | 1 | 3 | LM3671 | SOT-23-5 | LM3671MF-3.3/NOPB | LM3671MF-3.3/NOPBCT-ND | Check pinout at footprint assignment
 | U5 | 1 | 3 | PRTR5V0U2X | TO-253-4 | PRTR5V0U2X,215 | 568-4140-1-ND
 | Y1 | 1 | 3 | 32.768kHz | Custom | FC-135 32.7680KA-A5 | SER4103CT-ND | 12.5 pF
 | Y2 | 1 | 3 | 12MHz | HC49 | GC1200050 | GC1200050CT-ND | 16 pF
 | Cext = 2 × (Ccrystal - Cpara - Cpcb) |  | Cpara (RTC) = 0.7pF |  |  | Cpara (12 MHz) = <0.1pF
 | Ccrystal (RTC) must be 6 to 12.5 pF |  | Cext (RTC) = 2 * (12.5 pF - 0.7 pF - 0.5 pF) = 22.6 |  |  | Cext (12 MHz) = 2 * (16 pF - 9.5 - 0.5 pF) = 12 pF
 | Ccrystal (12 MHz) must be 12.5 to 17.5 pF
 | Cpcb (6 mil trace, 2 layer board above gnd plane, 1.6 mm, 4mm trace) = 0.5 pF. 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
